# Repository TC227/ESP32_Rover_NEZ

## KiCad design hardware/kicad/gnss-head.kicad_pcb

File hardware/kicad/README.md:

# เปิดวงจรนี้ใน KiCad

1. ติดตั้ง **KiCad 8 หรือ 9** (แนะนำ 9 — ไฟล์เป็น S-expression รุ่น 9)
2. **File → Open**
3. เลือก  
   `c:\project\ESP32_Rover_NEZ\hardware\kicad\gnss-head.kicad_pro`
4. เปิด **PCB Editor** — แผงพาหะ `gnss-head.kicad_pcb`
   - วงกลม **DIA 120 mm** ศูนย์กลาง `(60, 60)` — **K902 อยู่กลางเป๊ะ**
   - ด้านหน้า: K902 38×38 + ซ็อกเก็ตตัวเมีย 1×9+1×10 ห่าง 34 มม. + **J7 JST-PH 6P ตัวผู้สำรอง** + ESP32 ซ็อกเก็ตตัวเมีย 2×15
   - ด้านหลัง: USB-C 5V บนซ้าย (USB +Y แพด +/−/K) + HC-12 ใต้ K902 (เสา +X) + **BAT J5 PH2.0** + **J8 SW3 PWR PH2.0** (สวิตช์ภายนอก ไม่บัดกรี 6×6 บนแผง)
   - เปิดใน EasyEDA **Standard**: `easyeda/gnss-head.json` — File → Import → EasyEDA (ดู `easyeda/README.md`) ไม่ต้องใช้ Pro
5. สลับดูด้านหลัง: กด **B** หรือ View → Flip Board
6. **Edit → Fill All Zones** ครั้งหนึ่งหลังเปิด
7. อย่ากด Update PCB from Schematic ทับเลย์เอาต์นี้ — schematic ชุด SMT WROOM คนละสไตล์

สร้าง PCB ใหม่จากสคริปต์:

`python c:\project\ESP32_Rover_NEZ\hardware\kicad\gen_carrier_pcb.py`

GPIO16/17 = K902 COM2 TTL · GPIO26/27/25 = HC-12 · J5 แบตเป็น **PH2.0 ไม่ใช่ XH**

ลายปริ้น (ทองแดง) ส่งออกแล้วที่  
`hardware/kicad/plot/gnss-head-F_Cu.svg` (ด้านหน้า)  
`hardware/kicad/plot/gnss-head-B_Cu.svg` (ด้านหลัง พลิกกระจก)

สร้างใหม่: `python hardware/kicad/plot_copper_svg.py`  
ใน KiCad: **File → Plot** เลือก Gerber/SVG ชั้น F.Cu B.Cu Edge.Cuts แล้ว **Fill All Zones** ก่อนส่งโรงงาน

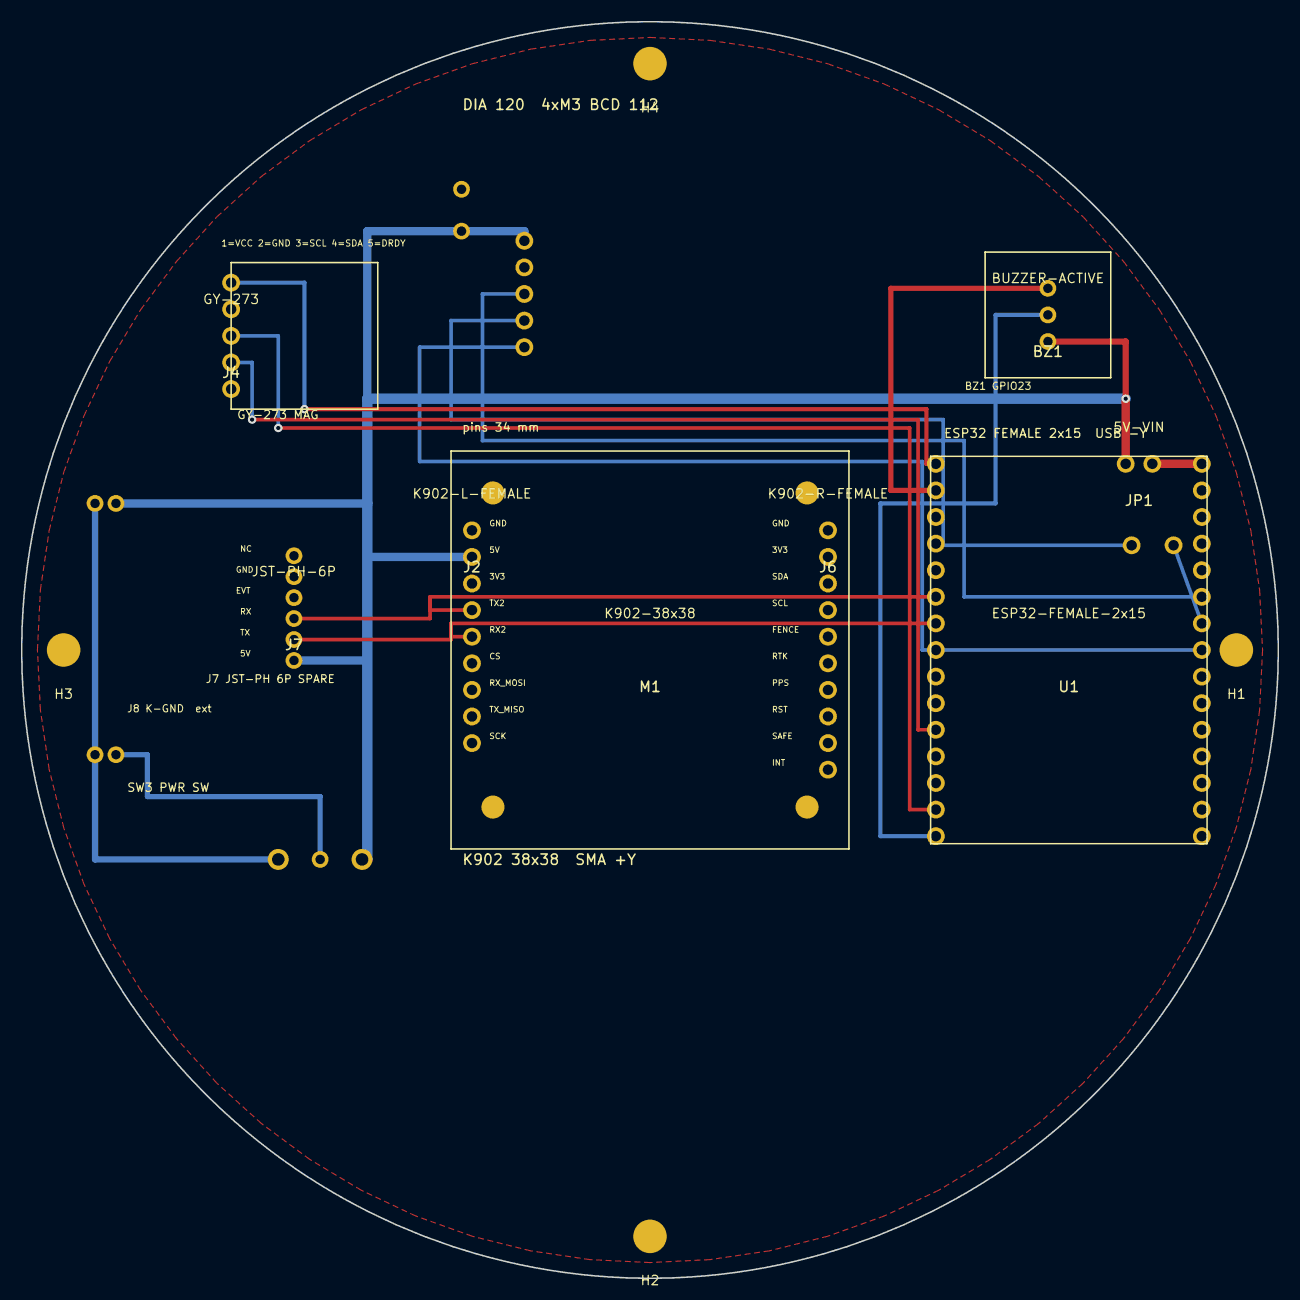
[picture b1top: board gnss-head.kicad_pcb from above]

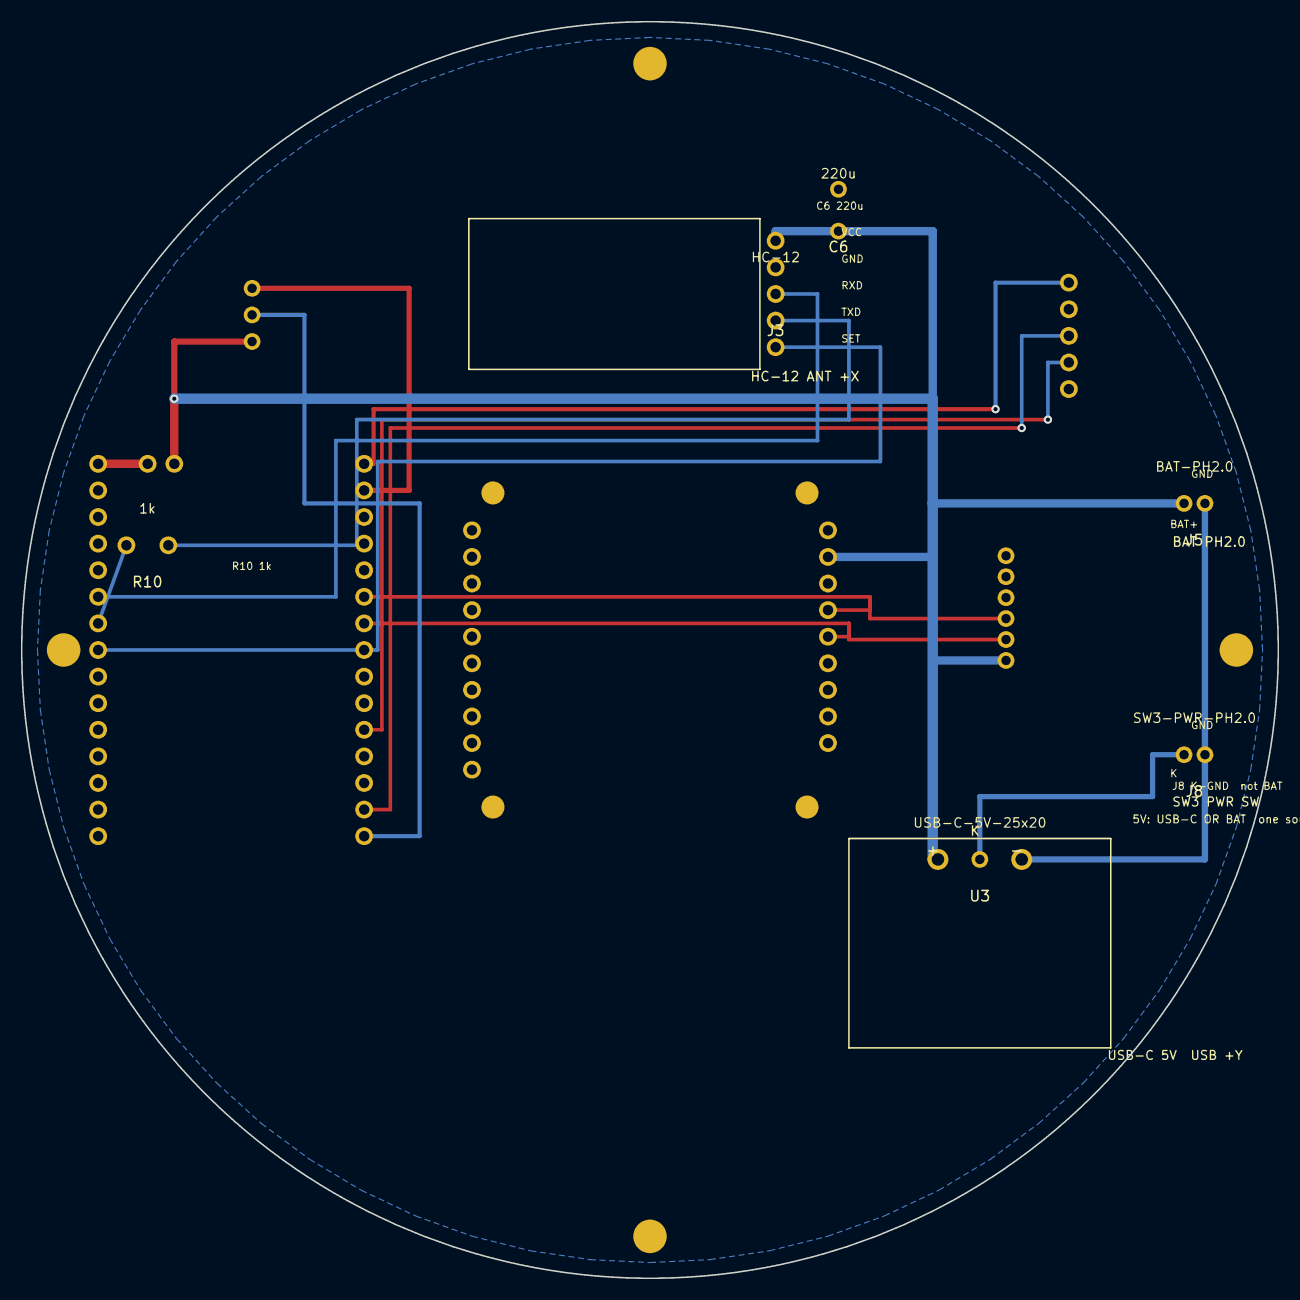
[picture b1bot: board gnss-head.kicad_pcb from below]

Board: 2 copper layers, 120.0 x 120.0 mm, 18 parts (6 on the bottom side), 14 nets.

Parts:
BZ1: BUZZER-ACTIVE; BUZZER_3P
C6: 220u; CP_Radial_D5.0mm_P2.50mm
H1, H2, H3, H4: M3; MountingHole_3.2mm_M3
J2: K902-L-FEMALE; PinSocket_1x09_P2.54mm_Vertical
J3: HC-12; HC12_1x05
J4: GY-273; PinSocket_1x05_P2.54mm_Vertical
J5: BAT-PH2.0; JST_PH_B2B-PH-K_1x02_P2.00mm_Vertical
J6: K902-R-FEMALE; PinSocket_1x10_P2.54mm_Vertical
J7: JST-PH-6P; JST_PH_B6B-PH-K_1x06_P2.00mm_Vertical
J8: SW3-PWR-PH2.0; JST_PH_B2B-PH-K_1x02_P2.00mm_Vertical
JP1: 5V-VIN; PinHeader_1x02_P2.54mm_Vertical
M1: K902-38x38; K902_38x38
R10: 1k; R_Axial_DIN0207_L6.3mm_D2.5mm_P7.62mm_Horizontal
U1: ESP32-FEMALE-2x15; ESP32_DevKit_FEMALE_2x15
U3: USB-C-5V-25x20; USBC_5V_25x20

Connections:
3V3: J4.1, U1.3V3
5V: BZ1.VCC, C6.1, J2.8, J3.1, J5.1, J7.1, JP1.1, U3.+
BUZZER: BZ1.IO, U1.23
GND: BZ1.GND, C6.2, J2.9, J3.2, J4.2, J5.2, J6.10, J7.5, J8.2, U1.GND, U1.GND2, U3.-
HC12_SET: J3.5, U1.25
I2C_SCL: J4.3, U1.22
I2C_SDA: J4.4, U1.21
PSU_K: J8.1, U3.K
UART1_RX: R10.1, U1.26
UART1_RX_HC: J3.4, R10.2
UART1_TX: J3.3, U1.27
UART2_RX: J2.6, J7.3, U1.16
UART2_TX: J2.5, J7.2, U1.17
VIN: JP1.2, U1.VIN

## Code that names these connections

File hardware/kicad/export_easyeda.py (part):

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    k902_left = [
        (str(i), k902_xl, k902_gnd_y + (9 - i) * pitch, net)
        for i, net in enumerate(
            ["", "", "", "", "UART2_TX", "UART2_RX", "", "5V", "GND"], start=1
        )
    ]
    k902_right = [
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    jp = (rx - 6.0, y0)
    jp_pins = [("1", jp[0] - 1.27, jp[1], "5V"), ("2", jp[0] + 1.27, jp[1], "VIN")]
    j5_pins = [("1", 9.0, 46.0, "5V"), ("2", 7.0, 46.0, "GND")]
    j8_pins = [("1", 9.0, 70.0, "PSU_K"), ("2", 7.0, 70.0, "GND")]
    j7_pins = [
        ("1", 26.0, 61.0, "5V"),
        ("2", 26.0, 59.0, "UART2_TX"),
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    ))
    shapes.append(header_device("J5", "JST-PH-2P", "CONN-TH_B2B-PH-K-S", j5_pins, "2", MODEL_PH2, "180,0,0", "-13.8"))
    shapes.append(header_device("J8", "SW3-PWR-PH2", "CONN-TH_B2B-PH-K-S", j8_pins, "2", MODEL_PH2, "180,0,0", "-13.8"))
    bz_pins = [("VCC", 98.0, 30.54, "5V"), ("IO", 98.0, 28.0, "BUZZER"), ("GND", 98.0, 25.46, "GND")]
    shapes.append(header_device("BZ1", "BUZZER-ACTIVE", "BUZZER_3P", bz_pins, "1", None, "0,0,0", "-11.8"))
    shapes.append(module_device(
        "R10", "1k", "R_Axial_P7.62", (106, 48.5, 110, 51.5), "2",
        extra_pads=[("1", 110.0, 50.0, "UART1_RX"), ("2", 106.0, 50.0, "UART1_RX_HC")],
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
